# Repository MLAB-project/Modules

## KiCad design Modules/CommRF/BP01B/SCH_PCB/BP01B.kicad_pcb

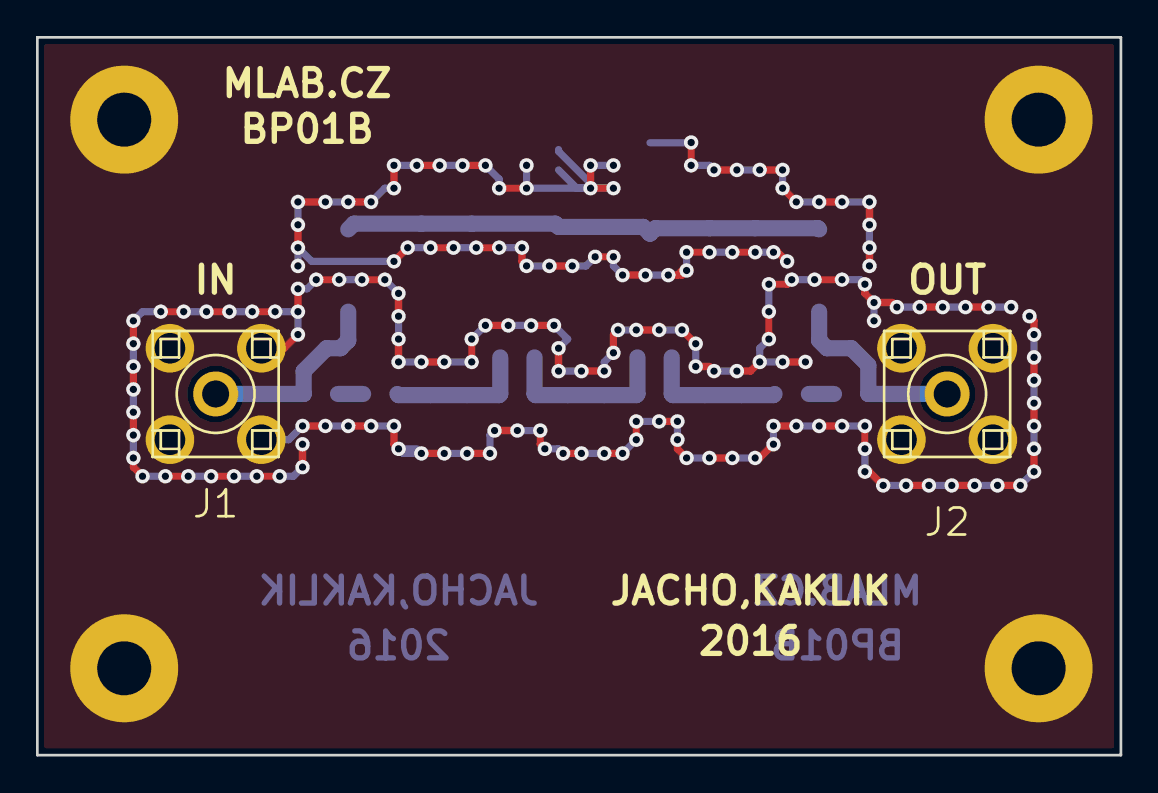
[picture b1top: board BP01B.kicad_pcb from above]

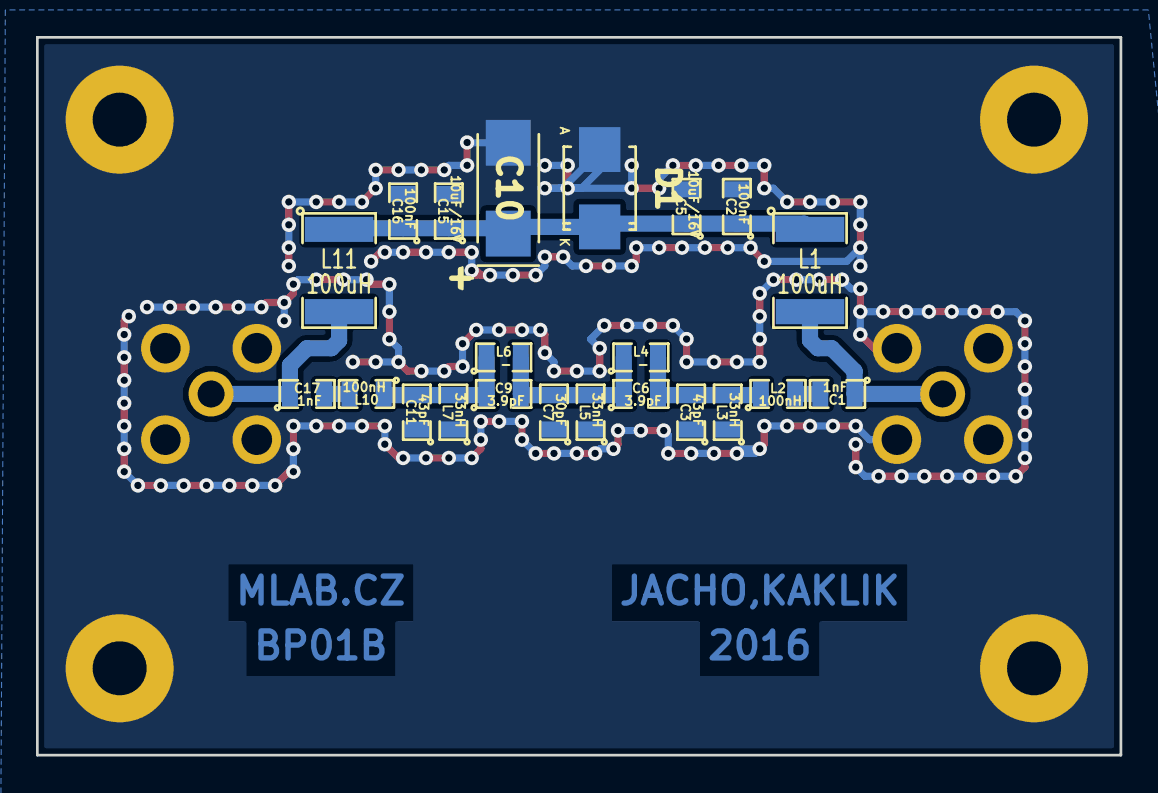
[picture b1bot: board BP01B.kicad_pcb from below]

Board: 2 copper layers, 60.2 x 39.9 mm, 28 parts (22 on the bottom side), 9 nets.

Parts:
C1, C17: 1nF; SMD-0805
C2, C16: 100nF; SMD-0805
C3, C11: 43pF; SMD-0805
C5, C15: 10uF/16V; SMD-0805
C6, C9: 3.9pF; SMD-0805
C7: 30pF; SMD-0805
C10: 47uF/16V; TantalC_SizeC_Reflow
D1: SMBJ15A-E3/52; SMB_Standard
J1, J2: SMA6251A13G50
L1, L11: 100uH; SMD-1812
L2, L10: 100nH; SMD-0805
L3, L5, L7: 33nH; SMD-0805
L4, L6: -; SMD-0805
M1, M2, M3, M4: HOLE; MountingHole_3mm

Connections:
GND: C2.2, C3.1, C5.2, C7.1, C10.2, C11.1, C15.2, C16.2, D1.2, J1.2, J2.2, L3.1, L5.1, L7.1, M1.1, M2.1, M3.1, M4.1
unnamed: C1.1, J1.1, L1.2
unnamed: C1.2, L2.2
unnamed: C3.2, C6.2, L2.1, L3.2, L4.2
unnamed: C6.1, C7.2, C9.2, L4.1, L5.2, L6.2
unnamed: C2.1, C5.1, C10.1, C15.1, C16.1, D1.1, L1.1, L11.1
unnamed: C9.1, C11.2, L6.1, L7.2, L10.1
unnamed: C17.1, J2.1, L11.2
unnamed: C17.2, L10.2

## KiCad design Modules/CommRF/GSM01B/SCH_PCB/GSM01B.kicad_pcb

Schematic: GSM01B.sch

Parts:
C1: 1F; C_Radial_D8_L11.5_P3.5
C2: 470uF/6.3V; TantalC_SizeD_Reflow
C3, C8, C9, C10, C11: 47pF; SMD-0805
C4, C12: 100nF; SMD-0805
C5: 10nF; SMD-0805
C6: 39pF; SMD-0805
C7: 10pF; SMD-0805
D1: BZV55C-3,6V; Diode-MiniMELF_Standard
D2, D3: LED; LED_1206
D4: M4; Diode-SMA_Standard
J1, J2, J3, J4, J5, J6, J7, J8, J9, J10, J11, J12, J14, J15, J16, J17, J18, J19, J20, J21, J22, J23, J24, J25, J26, J27, J28, J29, J30, J31, J32, J33, J34: JUMP_2x1; Straight_1x02
J13: SMA; SMA6251A13G50
J35: SIMCN-8P
J36, J37: JUMP2_2x1; Straight_1x02
J38: JUMP_3X2; Straight_2x03
L1: BLM21PG300SN1; SMD-0805
M1, M2, M3, M4: HOLE; MountingHole_3mm
Q1, Q2: MMBF170LT1G; SOT-23
R1, R3, R4: 4k7; SMD-0805
R2, R9, R10: 100k; SMD-0805
R5, R6: 1k; SMD-0805
R7, R8: 330k; SMD-0805
SW1, SW2: SW_PUSH; SW_PUSH_SMALL
U1: LEON100; LEON-G1

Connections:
/ADC1: D1.1, J14.1, J14.2, U1.5 (ADC1)
/CTS: J8.1, J8.2, U1.14 (CTS)
/DCD: J5.1, J5.2, U1.11 (DCD)
/DSR: J3.1, J3.2, U1.9 (DSR)
/DTR: J6.1, J6.2, U1.12 (DTR)
/GPIO01: J15.1, J15.2, J36.1, U1.20 (GPIO1)
/GPIO02: J16.1, J16.2, J37.1, U1.21 (GPIO2)
/GPIO03: J17.1, J17.2, U1.23 (GPIO3)
/GPIO04: J18.1, J18.2, U1.24 (GPIO4)
/HS_DET: J11.1, J11.2, U1.18 (HS_DET)
/HS_P: J21.1, J21.2, U1.37 (HS_P)
/I2S_CLK: J23.1, J23.2, U1.28 (I2S_CLK)
/I2S_RXD: J22.1, J22.2, U1.29 (I2S_RXD)
/I2S_TXD: J24.1, J24.2, U1.27 (I2S_TXD)
/I2S_WA: J25.1, J25.2, U1.26 (I2S_WA)
/MIC_BIAS1: J26.1, J26.2, U1.44 (MIC_BIAS1)
/MIC_BIAS2: J29.1, J29.2, U1.41 (MIC_BIAS2)
/MIC_GND1: J27.1, J27.2, U1.43 (MIC_GND1)
/MIC_GND2: J28.1, J28.2, U1.42 (MIC_GND2)
/PWR_ON: J1.1, J1.2, R2.2, SW1.2, U1.19 (PWR_ON)
/RESET: C3.1, J2.1, J2.2, L1.1, SW2.2
/RI: J4.1, J4.2, U1.10 (RI)
/RTS: J7.1, J7.2, U1.13 (RTS)
/RXD: J10.1, J10.2, U1.16 (RXD)
/SCL: J32.1, J32.2, R3.2, U1.30 (SCL)
/SDA: J31.1, J31.2, R4.2, U1.31 (SDA)
/SPK_N: J19.1, J19.2, U1.39 (SPK_N)
/SPK_P: J20.1, J20.2, U1.38 (SPK_P)
/TXD: J9.1, J9.2, U1.15 (TXD)
/V_BCKP: R1.1, R2.1, U1.2 (V_BCKP)
GND: C1.2, C2.2, C3.2, C4.2, C5.2, C6.2, C7.2, C8.2, C9.2, C10.2, C11.2, C12.2, D1.2, D4.1, J12.1, J12.2, J13.2, J33.1, J33.2, J34.1, J34.2, J35.5, J38.1, J38.2, J38.5, J38.6, M1.1, M2.1, M3.1, M4.1, Q1.S, Q2.S, R7.2, R8.2, SW1.1, SW2.1, U1.1 (GND), U1.3 (GND), U1.6 (GND), U1.7 (GND), U1.8 (GND), U1.17 (GND), U1.25 (GND), U1.36 (GND), U1.45 (GND), U1.46 (GND), U1.48 (GND), U1.49 (GND)
unnamed: C1.1, R1.2
unnamed: C8.1, J35.2, U1.34 (SIM_RST)
unnamed: C9.1, J35.3, U1.32 (SIM_CLK)
unnamed: C10.1, J35.7, U1.33 (SIM_IO)
unnamed: C11.1, C12.1, J35.1, J35.6, U1.35 (VSIM)
unnamed: D2.1, Q1.D
unnamed: D2.2, R5.2
unnamed: D3.1, Q2.D
unnamed: D3.2, R6.2
unnamed: J13.1, U1.47 (ANT)
unnamed: J30.1, J30.2, R3.1, R4.1
unnamed: J36.2, R9.1
unnamed: J37.2, R10.1
unnamed: L1.2, U1.22 (RESET_N)
unnamed: Q1.G, R7.1, R9.2
unnamed: Q2.G, R8.1, R10.2
VCC: C2.1, C4.1, C5.1, C6.1, C7.1, D4.2, J38.3, J38.4, R5.1, R6.1, U1.50 (VCC)

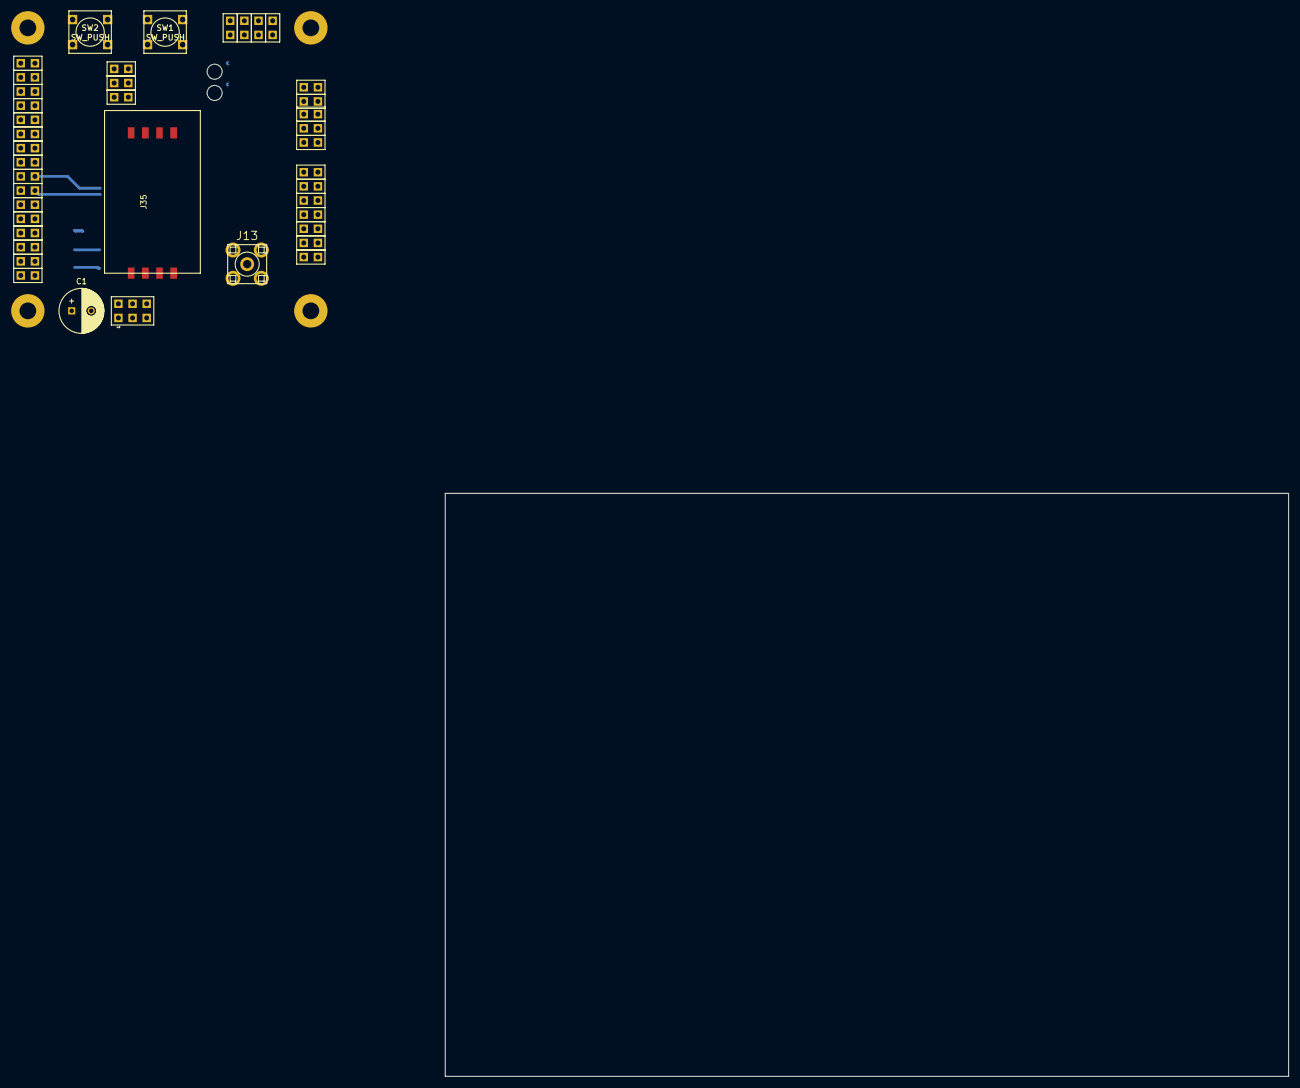
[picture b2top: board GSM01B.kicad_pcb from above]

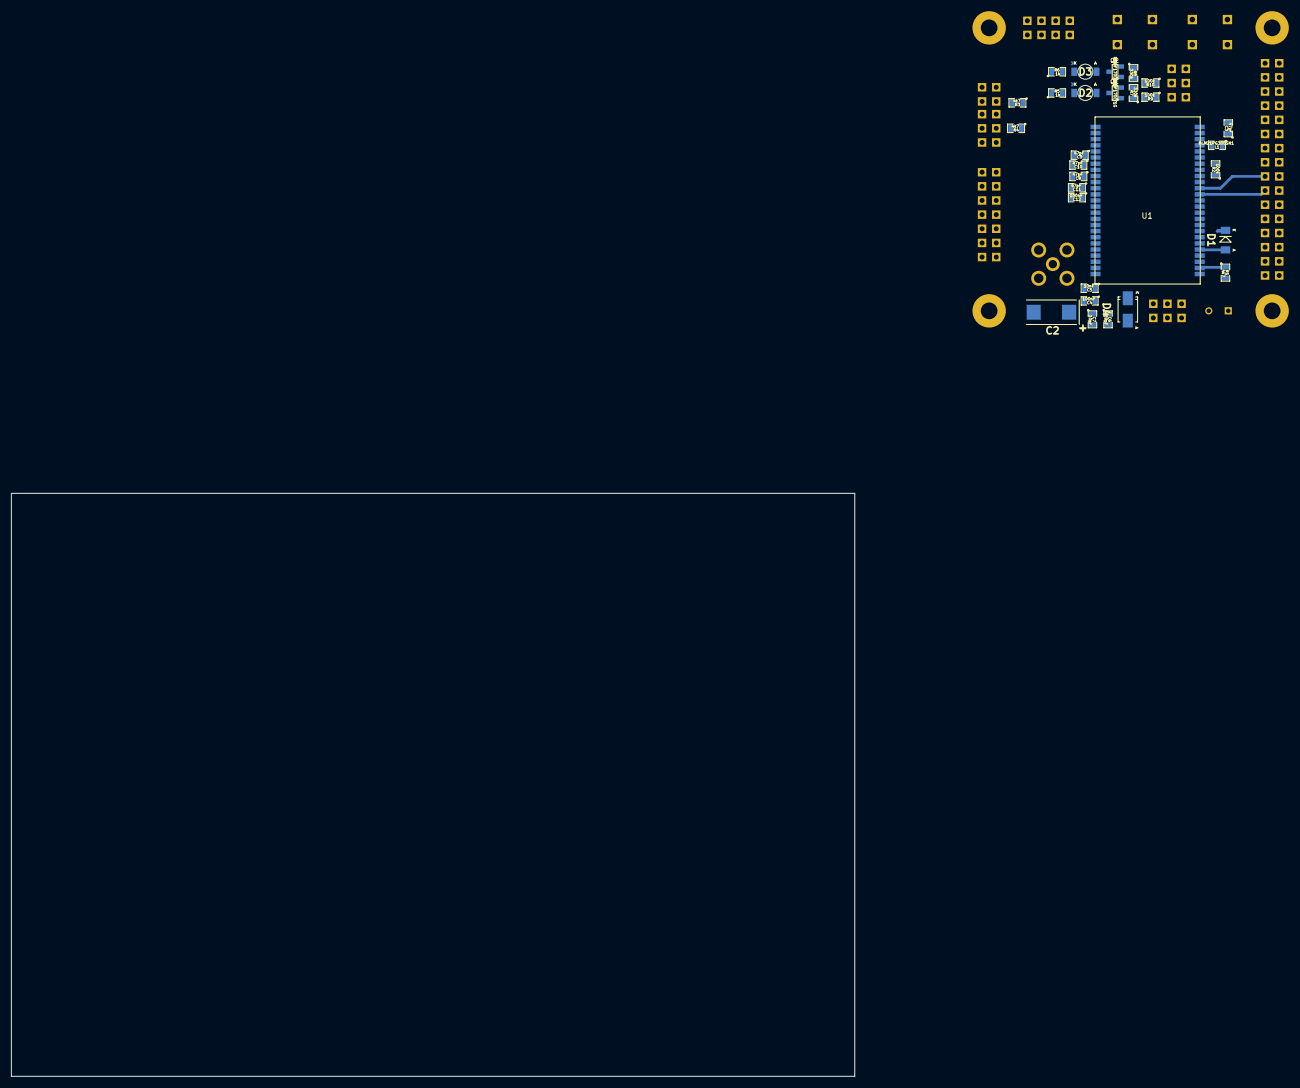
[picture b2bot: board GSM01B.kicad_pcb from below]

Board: 2 copper layers, 151.4 x 104.6 mm, 74 parts (29 on the bottom side), 48 nets.

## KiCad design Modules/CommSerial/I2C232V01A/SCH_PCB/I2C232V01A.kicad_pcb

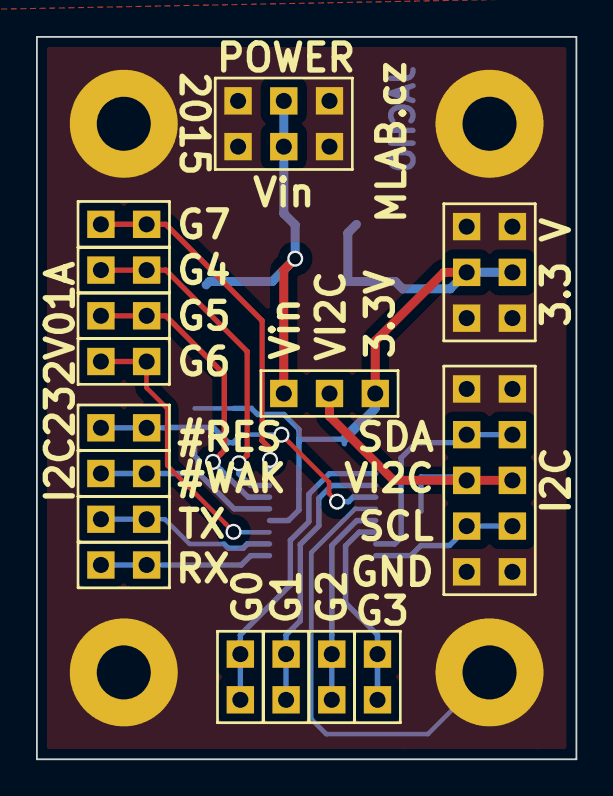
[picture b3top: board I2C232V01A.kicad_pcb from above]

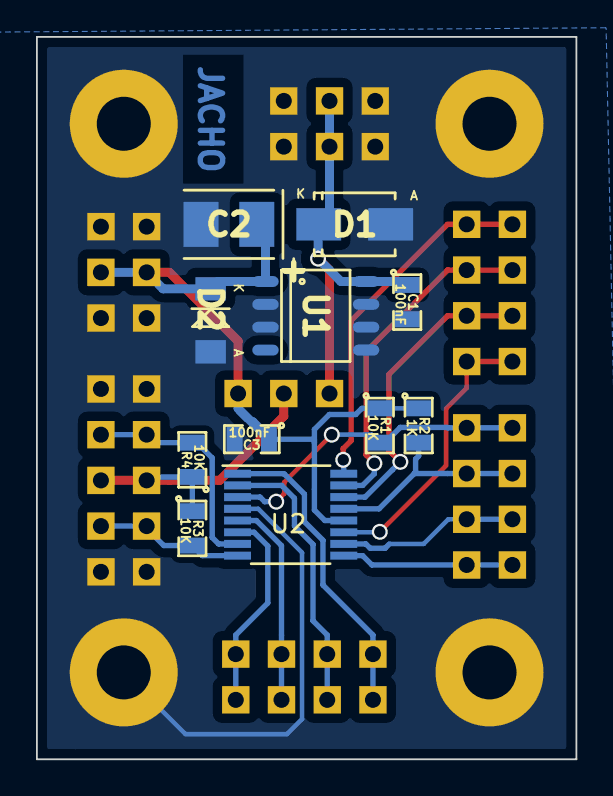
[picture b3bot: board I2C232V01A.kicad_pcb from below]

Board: 2 copper layers, 30.0 x 40.1 mm, 31 parts (11 on the bottom side), 18 nets.

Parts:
C1, C3: 100nF; SMD-0805
C2: 10uF; TantalC_SizeB_Reflow
D1: M4; SMA_Standard
D2: BZV55C-3,6V; MiniMELF_Standard
J1, J6: JUMP_3X2; Straight_2x03
J2, J3, J4, J5, J7, J8, J9, J10, J11, J12, J13, J14: JUMP_2x1; Straight_2x01
J15: CONN_3; Straight_1x03
J16: JUMP_5X2; Straight_2x05
P1, P2, P3, P4: sroub; MountingHole_3mm
R1, R3, R4: 10K; SMD-0805
R2: 1K; SMD-0805
U1: LE33CD; SO-8
U2: SC18IM700; TSSOP-16_4.4x5mm_Pitch0.65mm

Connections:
+3V3: C2.1, C3.1, D2.2, J6.3, J6.4, J15.1, R1.1, R2.1, U1.1, U2.12
/#RES: J4.1, J4.2, R1.2, U2.3
/#WAK: J5.1, J5.2, R2.2, U2.13
/G0: J7.1, J7.2, U2.1
/G1: J8.1, J8.2, U2.2
/G2: J9.1, J9.2, U2.5
/G3: J10.1, J10.2, U2.6
/G4: J11.1, J11.2, U2.15
/G5: J12.1, J12.2, U2.14
/G6: J13.1, J13.2, U2.11
/G7: J14.1, J14.2, U2.16
/RX: J3.1, J3.2, U2.9
/SCL: J16.7, J16.8, R3.2, U2.8
/SDA: J16.3, J16.4, R4.2, U2.7
/TX: J2.1, J2.2, U2.10
GND: C1.2, C2.2, C3.2, D1.1, D2.1, J1.1, J1.2, J1.5, J1.6, J6.1, J6.2, J6.5, J6.6, J16.1, J16.2, J16.9, J16.10, P1.1, P2.1, P3.1, P4.1, U1.2, U1.3, U1.5, U1.6, U1.7, U2.4
unnamed: J15.2, J16.5, J16.6, R3.1, R4.1
VCC: C1.1, D1.2, J1.3, J1.4, J15.3, U1.8

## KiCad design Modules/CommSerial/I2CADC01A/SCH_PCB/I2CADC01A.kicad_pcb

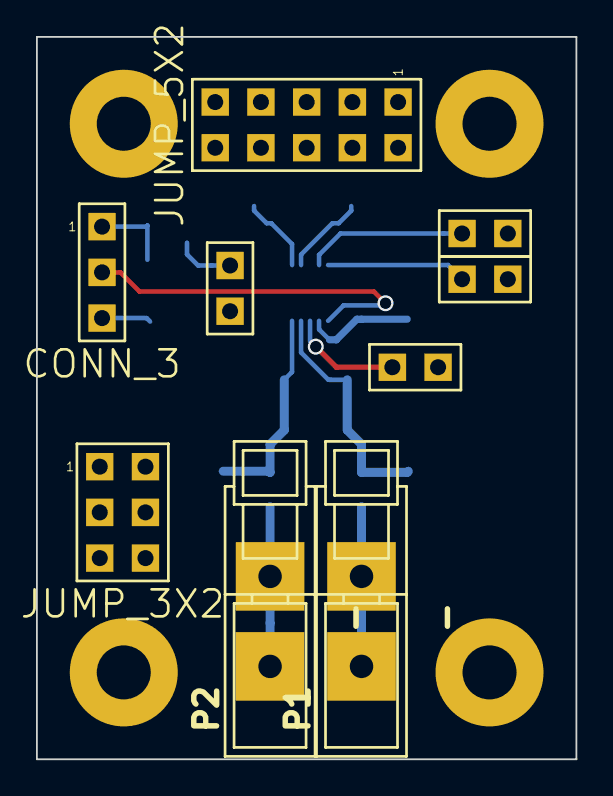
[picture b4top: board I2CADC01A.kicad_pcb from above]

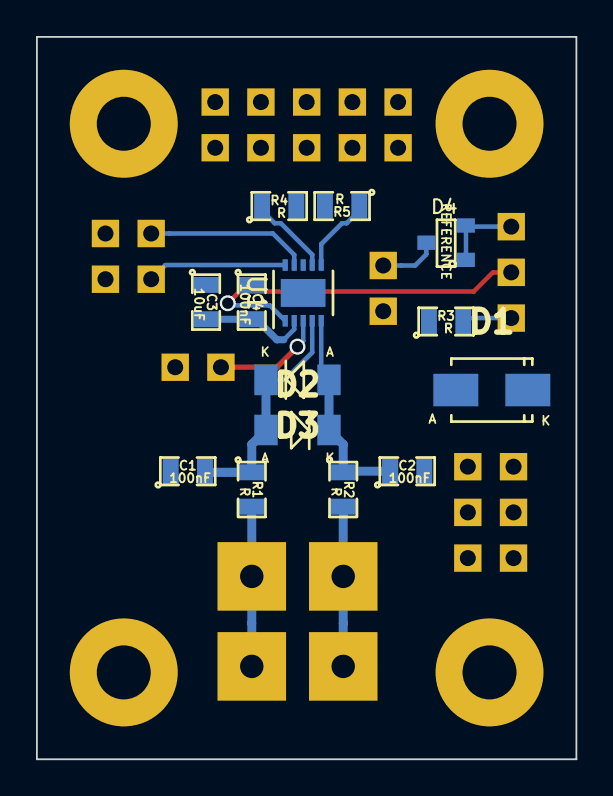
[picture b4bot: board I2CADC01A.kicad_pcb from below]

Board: 2 copper layers, 30.0 x 40.1 mm, 27 parts (14 on the bottom side), 13 nets.

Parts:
C1, C2, C4: 100nF; SMD-0805
C3: 10uF; SMD-0805
D1: M4; SMA_Standard
D2, D3: BAT46; MiniMELF_Standard
D4: REFERENCE; SOT-23
J1: JUMP_3X2; Straight_2x03
J2: CONN1_2; Straight_2x01
J3: CONN_2; Straight_2x01
J4: CONN_3; Straight_1x03
J5, J6: JUMP2_2x1; Straight_2x01
J7: JUMP_5X2; Straight_2x05
M1, M2, M3, M4: HOLE; MountingHole_3mm
P1, P2: _; WAGO256
R1, R2, R3, R4, R5: R; SMD-0805
U1: LTC2485; DFN-10-1EP_3x3mm_Pitch0.5mm

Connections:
/CA0: J5.2, U1.10
/CA1: J6.2, U1.9
/SCL: J7.7, J7.8, R5.1, U1.6
/SDA: J7.3, J7.4, R4.1, U1.7
GND: C1.1, C2.2, C3.1, C4.1, D1.1, D4.3, J1.1, J1.2, J1.5, J1.6, J2.1, J3.1, J7.1, J7.2, J7.9, J7.10, M1.1, M2.1, M3.1, M4.1, U1.8, U1.11
unnamed: C1.2, D2.1, D3.2, R1.1, U1.4
unnamed: C2.1, D2.2, D3.1, J2.2, R2.1, U1.5
unnamed: D4.1, D4.2, J4.1, R3.1
unnamed: J3.2, U1.3
unnamed: J4.2, U1.1
unnamed: P1.1, R1.2
unnamed: P2.1, R2.2
VCC: C3.2, C4.2, D1.2, J1.3, J1.4, J4.3, J5.1, J6.1, J7.5, J7.6, R3.2, R4.2, R5.2, U1.2

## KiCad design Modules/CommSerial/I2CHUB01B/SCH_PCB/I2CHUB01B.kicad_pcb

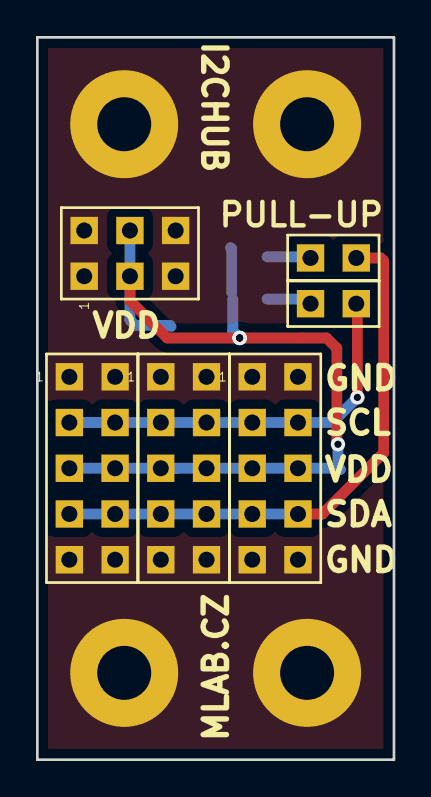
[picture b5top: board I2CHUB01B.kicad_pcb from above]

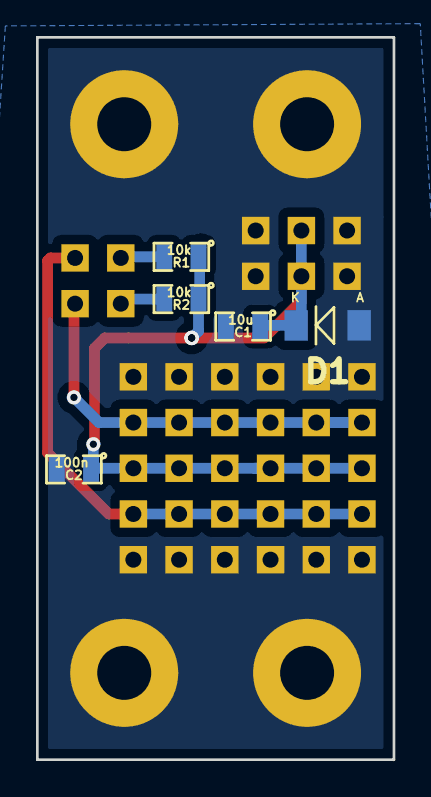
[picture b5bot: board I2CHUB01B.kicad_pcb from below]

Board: 2 copper layers, 19.8 x 40.1 mm, 15 parts (5 on the bottom side), 6 nets.

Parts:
C1: 10u; SMD-0805
C2: 100n; SMD-0805
D1: BZV55C; Diode-MiniMELF_Standard
J1: JUMP_3X2; Straight_2x03
J2, J3, J4: JUMP_5X2; Straight_2x05
J5, J6: CONN_2; Straight_1x02
M1, M2, M3, M4: HOLE; MountingHole_3mm
R1, R2: 10k; SMD-0805

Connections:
/SCL: J2.3, J2.4, J3.3, J3.4, J4.3, J4.4, J6.2
/SDA: J2.7, J2.8, J3.7, J3.8, J4.7, J4.8, J5.2
GND: C1.2, C2.2, D1.1, J1.1, J1.2, J1.5, J1.6, J2.1, J2.2, J2.9, J2.10, J3.1, J3.2, J3.9, J3.10, J4.1, J4.2, J4.9, J4.10, M1.1, M2.1, M3.1, M4.1
unnamed: J5.1, R1.2
unnamed: J6.1, R2.2
VCC: C1.1, C2.1, D1.2, J1.3, J1.4, J2.5, J2.6, J3.5, J3.6, J4.5, J4.6, R1.1, R2.1

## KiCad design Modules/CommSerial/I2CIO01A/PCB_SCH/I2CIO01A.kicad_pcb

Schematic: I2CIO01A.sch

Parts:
C1: 10uF; SMD-0805
C2: 100nF; SMD-0805
D1: ZENER; Diode-MiniMELF_Standard
J1: JUMP_2X2; Pin_Header_Straight_2x02
J2: JUMP_5X2; Pin_Header_Straight_2x05
J3: JUMP_3X2; Pin_Header_Straight_2x03
J4, J9: CONN_2; Pin_Header_Straight_1x02
J5, J8: CONN1_2; Pin_Header_Straight_1x02
J6, J7: JUMP_8X2; Pin_Header_Straight_2x08
P1, P2, P3, P4: _; MountingHole_3mm
R1, R2, R3, R4, R5, R7, R9, R11, R13, R15, R16, R18, R24: 10k; SMD-0805
R6, R8, R10, R12, R14, R17, R19, R20: -; SMD-0805
U1: TCA6416A; TSSOP-28

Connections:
/#INT: J1.2 (1), J1.3, R2.2, U1.1 (INT)
/#RES: J1.1, J1.4, J4.1, R4.2, U1.3 (RESET)
/A0: J9.2, R24.2, U1.21 (ADDR)
/P00: J6.1, J6.16, R18.2, U1.4 (P00)
/P01: J6.2, J6.15, R15.2, U1.5 (P01)
/P02: J6.3, J6.14, R16.2, U1.6 (P02)
/P03: J6.4, J6.13, R13.2, U1.7 (P03)
/P04: J6.5, J6.12, R11.2, U1.8 (P04)
/P05: J6.6, J6.11, R9.2, U1.9 (P05)
/P06: J6.7, J6.10, R7.2, U1.10 (P06)
/P07: J6.8, J6.9, R5.2, U1.11 (P07)
/P10: J7.1, J7.16, R20.2, U1.13 (P10)
/P11: J7.2, J7.15, R19.2, U1.14 (P11)
/P12: J7.3, J7.14, R17.2, U1.15 (P12)
/P13: J7.4, J7.13, R8.2, U1.16 (P13)
/P14: J7.5, J7.12, R12.2, U1.17 (P14)
/P15: J7.6, J7.11, R10.2, U1.18 (P15)
/P16: J7.7, J7.10, R14.2, U1.19 (P16)
/P17: J7.8, J7.9, R6.2, U1.20 (P17)
/SCL: J2.2, J2.9, R1.2, U1.22 (SCL)
/SDA: J2.4, J2.7, R3.2, U1.23 (SDA)
/Vccp: J5.2 (PM), R5.1, R6.1, R7.1, R8.1, R9.1, R10.1, R11.1, R12.1, R13.1, R14.1, R15.1, R16.1, R17.1, R18.1, R19.1, R20.1, U1.24 (Vccp)
GND: C1.2, C2.2, D1.1 (A), J2.1, J2.5, J2.6, J2.10, J3.1, J3.3, J3.4, J3.6, J4.2, J9.1, P1.1, P2.1, P3.1, P4.1, U1.12 (GND)
unnamed: J2.3, J2.8, J8.1, R1.1, R3.1
VDD: C1.1, C2.1, D1.2 (K), J3.2 (1), J3.5, J5.1, J8.2 (PM), R2.1, R4.1, R24.1, U1.2 (Vcci)

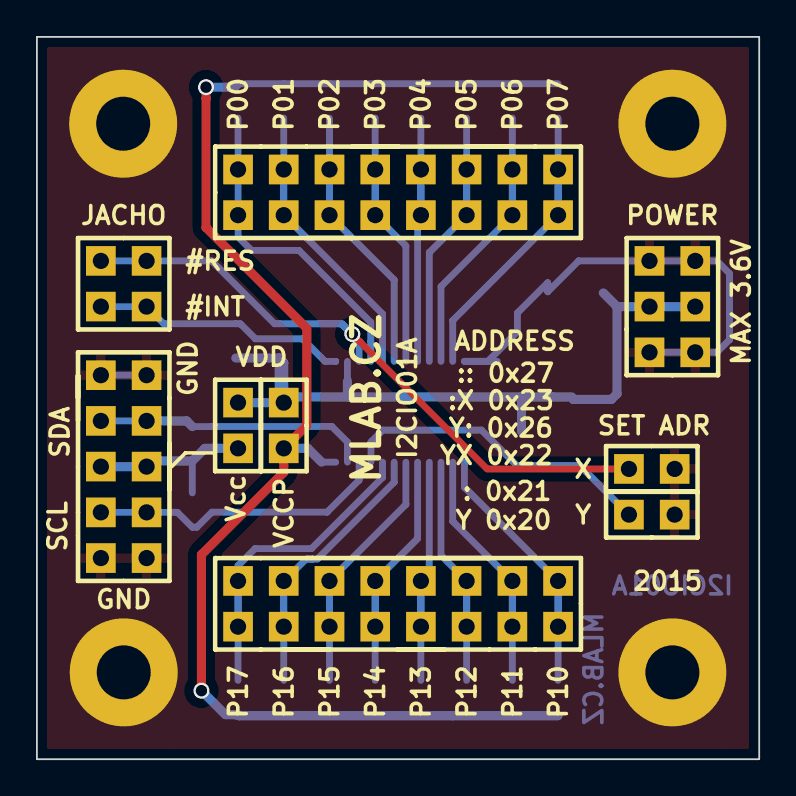
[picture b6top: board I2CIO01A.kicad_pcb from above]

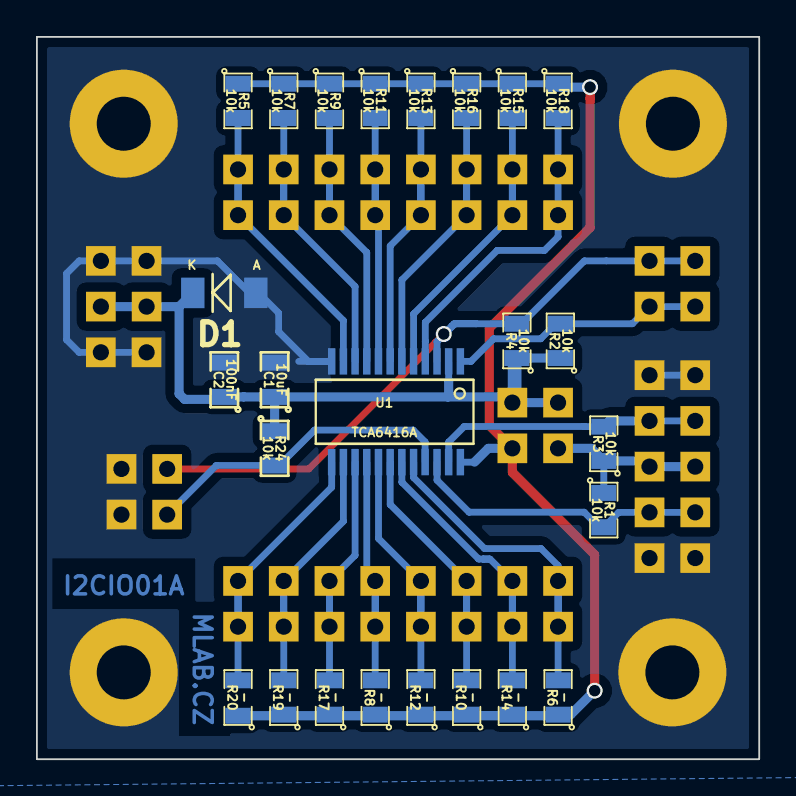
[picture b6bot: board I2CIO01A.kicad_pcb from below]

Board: 2 copper layers, 40.1 x 40.1 mm, 38 parts (25 on the bottom side), 25 nets.

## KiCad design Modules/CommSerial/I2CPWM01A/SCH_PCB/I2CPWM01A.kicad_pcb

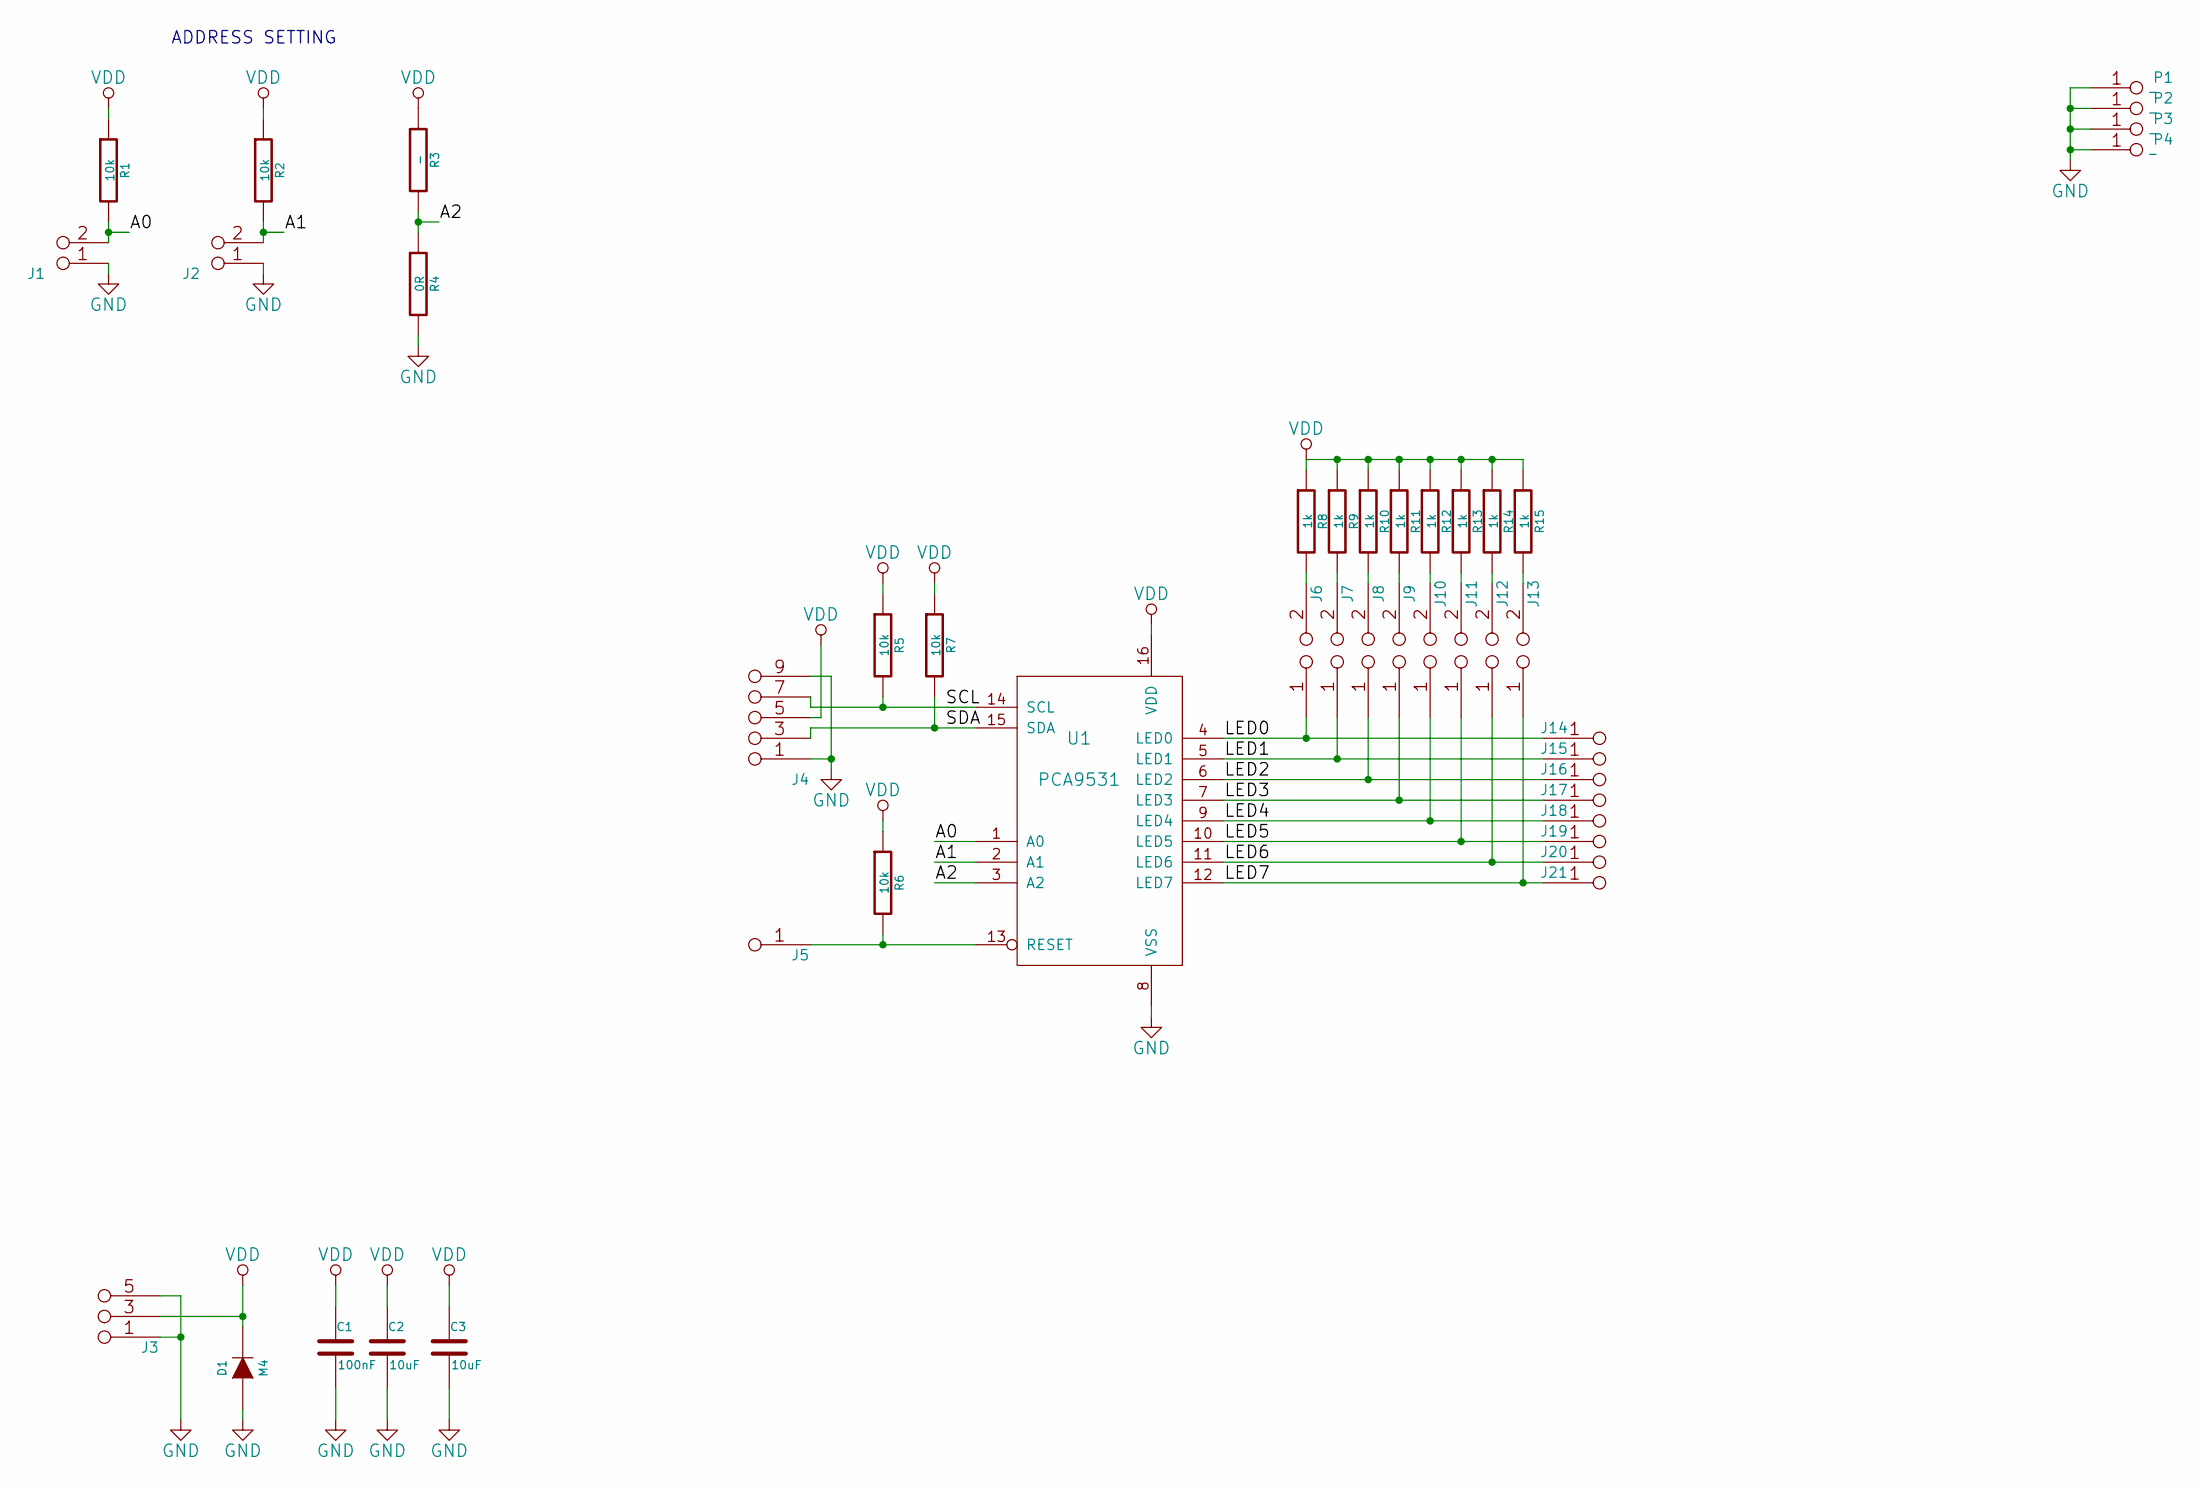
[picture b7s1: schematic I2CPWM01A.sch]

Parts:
C1: 100nF; SMD-0805
C2, C3: 10uF; SMD-0805
D1: M4; SMA_Standard
J1, J2: CONN1_2; Straight_2x01
J3: JUMP_3X2; Straight_2x03
J4: JUMP_5X2; Straight_2x05
J5, J14, J15, J16, J17, J18, J19, J20, J21: JUMP_2x1; Straight_2x01
J6, J7, J8, J9, J10, J11, J12, J13: JUMP2_2x1; Straight_2x01
P1, P2, P3, P4: _; MountingHole_3mm
R1, R2, R5, R6, R7: 10k; SMD-0805
R3: -; SMD-0805
R4: 0R; SMD-0805
R8, R9, R10, R11, R12, R13, R14, R15: 1k; SMD-0805
U1: PCA9531; TSSOP-16_4.4x5mm_Pitch0.65mm

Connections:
/A0: J1.2 (PM), R1.2, U1.1 (A0)
/A1: J2.2 (PM), R2.2, U1.2 (A1)
/A2: R3.2, R4.1, U1.3 (A2)
/LED0: J6.1, J14.1, J14.2, U1.4 (LED0)
/LED1: J7.1, J15.1, J15.2, U1.5 (LED1)
/LED2: J8.1, J16.1, J16.2, U1.6 (LED2)
/LED3: J9.1, J17.1, J17.2, U1.7 (LED3)
/LED4: J10.1, J18.1, J18.2, U1.9 (LED4)
/LED5: J11.1, J19.1, J19.2, U1.10 (LED5)
/LED6: J12.1, J20.1, J20.2, U1.11 (LED6)
/LED7: J13.1, J21.1, J21.2, U1.12 (LED7)
/SCL: J4.7, J4.8 (7), R5.2, U1.14 (SCL)
/SDA: J4.3 (4), J4.4, R7.2, U1.15 (SDA)
GND: C1.2, C2.2, C3.2, D1.1 (A), J1.1, J2.1, J3.1 (2), J3.2, J3.5 (6), J3.6, J4.1 (2), J4.2, J4.9 (10), J4.10, P1.1, P2.1, P3.1, P4.1, R4.2, U1.8 (VSS)
unnamed: J5.1, J5.2, R6.2, U1.13 (RESET)
unnamed: J6.2, R8.2
unnamed: J7.2, R9.2
unnamed: J8.2, R10.2
unnamed: J9.2, R11.2
unnamed: J10.2, R12.2
unnamed: J11.2, R13.2
unnamed: J12.2, R14.2
unnamed: J13.2, R15.2
VDD: C1.1, C2.1, C3.1, D1.2 (K), J3.3 (4), J3.4, J4.5 (6), J4.6, R1.1, R2.1, R3.1, R5.1, R6.1, R7.1, R8.1, R9.1, R10.1, R11.1, R12.1, R13.1, R14.1, R15.1, U1.16 (VDD)

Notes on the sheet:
ADDRESS SETTING

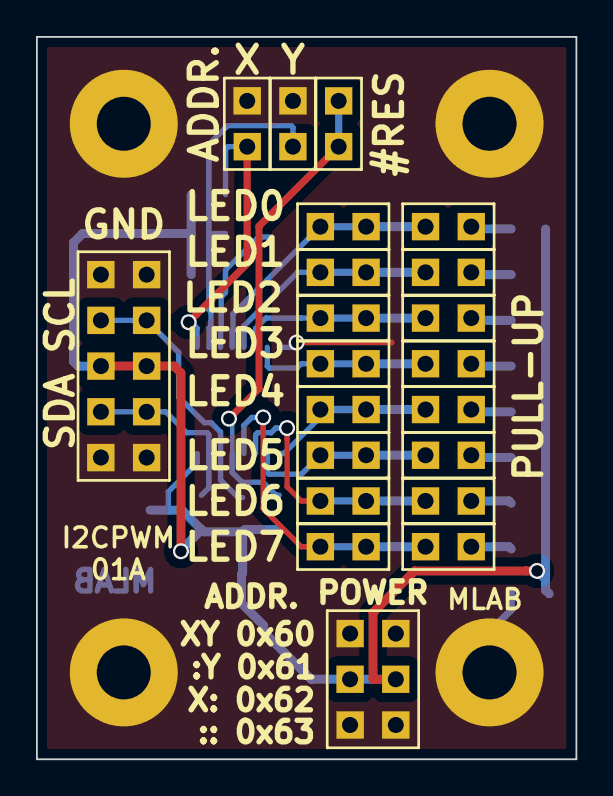
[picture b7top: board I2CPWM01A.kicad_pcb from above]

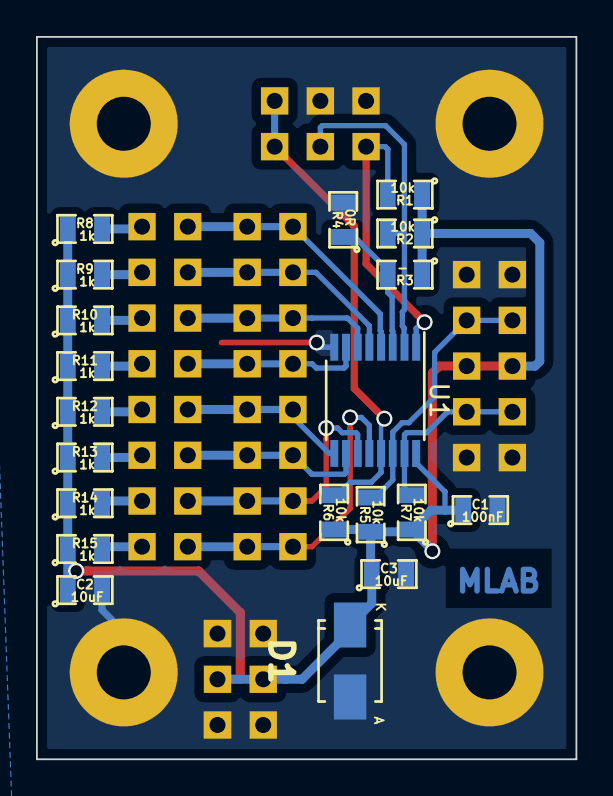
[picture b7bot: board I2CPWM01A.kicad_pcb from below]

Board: 2 copper layers, 30.0 x 40.1 mm, 45 parts (20 on the bottom side), 24 nets.
